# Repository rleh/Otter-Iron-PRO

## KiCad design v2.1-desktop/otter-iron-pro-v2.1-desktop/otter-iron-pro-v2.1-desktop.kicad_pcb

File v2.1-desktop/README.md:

# Otter-Iron-PRO v2.1-desktop

is variant of the _Otter-Iron-PRO v2.0_ designed for desktop-use.

Additional to/instead of USB-PD is can be supplied from any lab power supply with ?? to ?? V.
A cheap switch-mode mains power supply works as well, a stackable enclosure for a  _Meanwell RPS-???_ will be designed in the future.

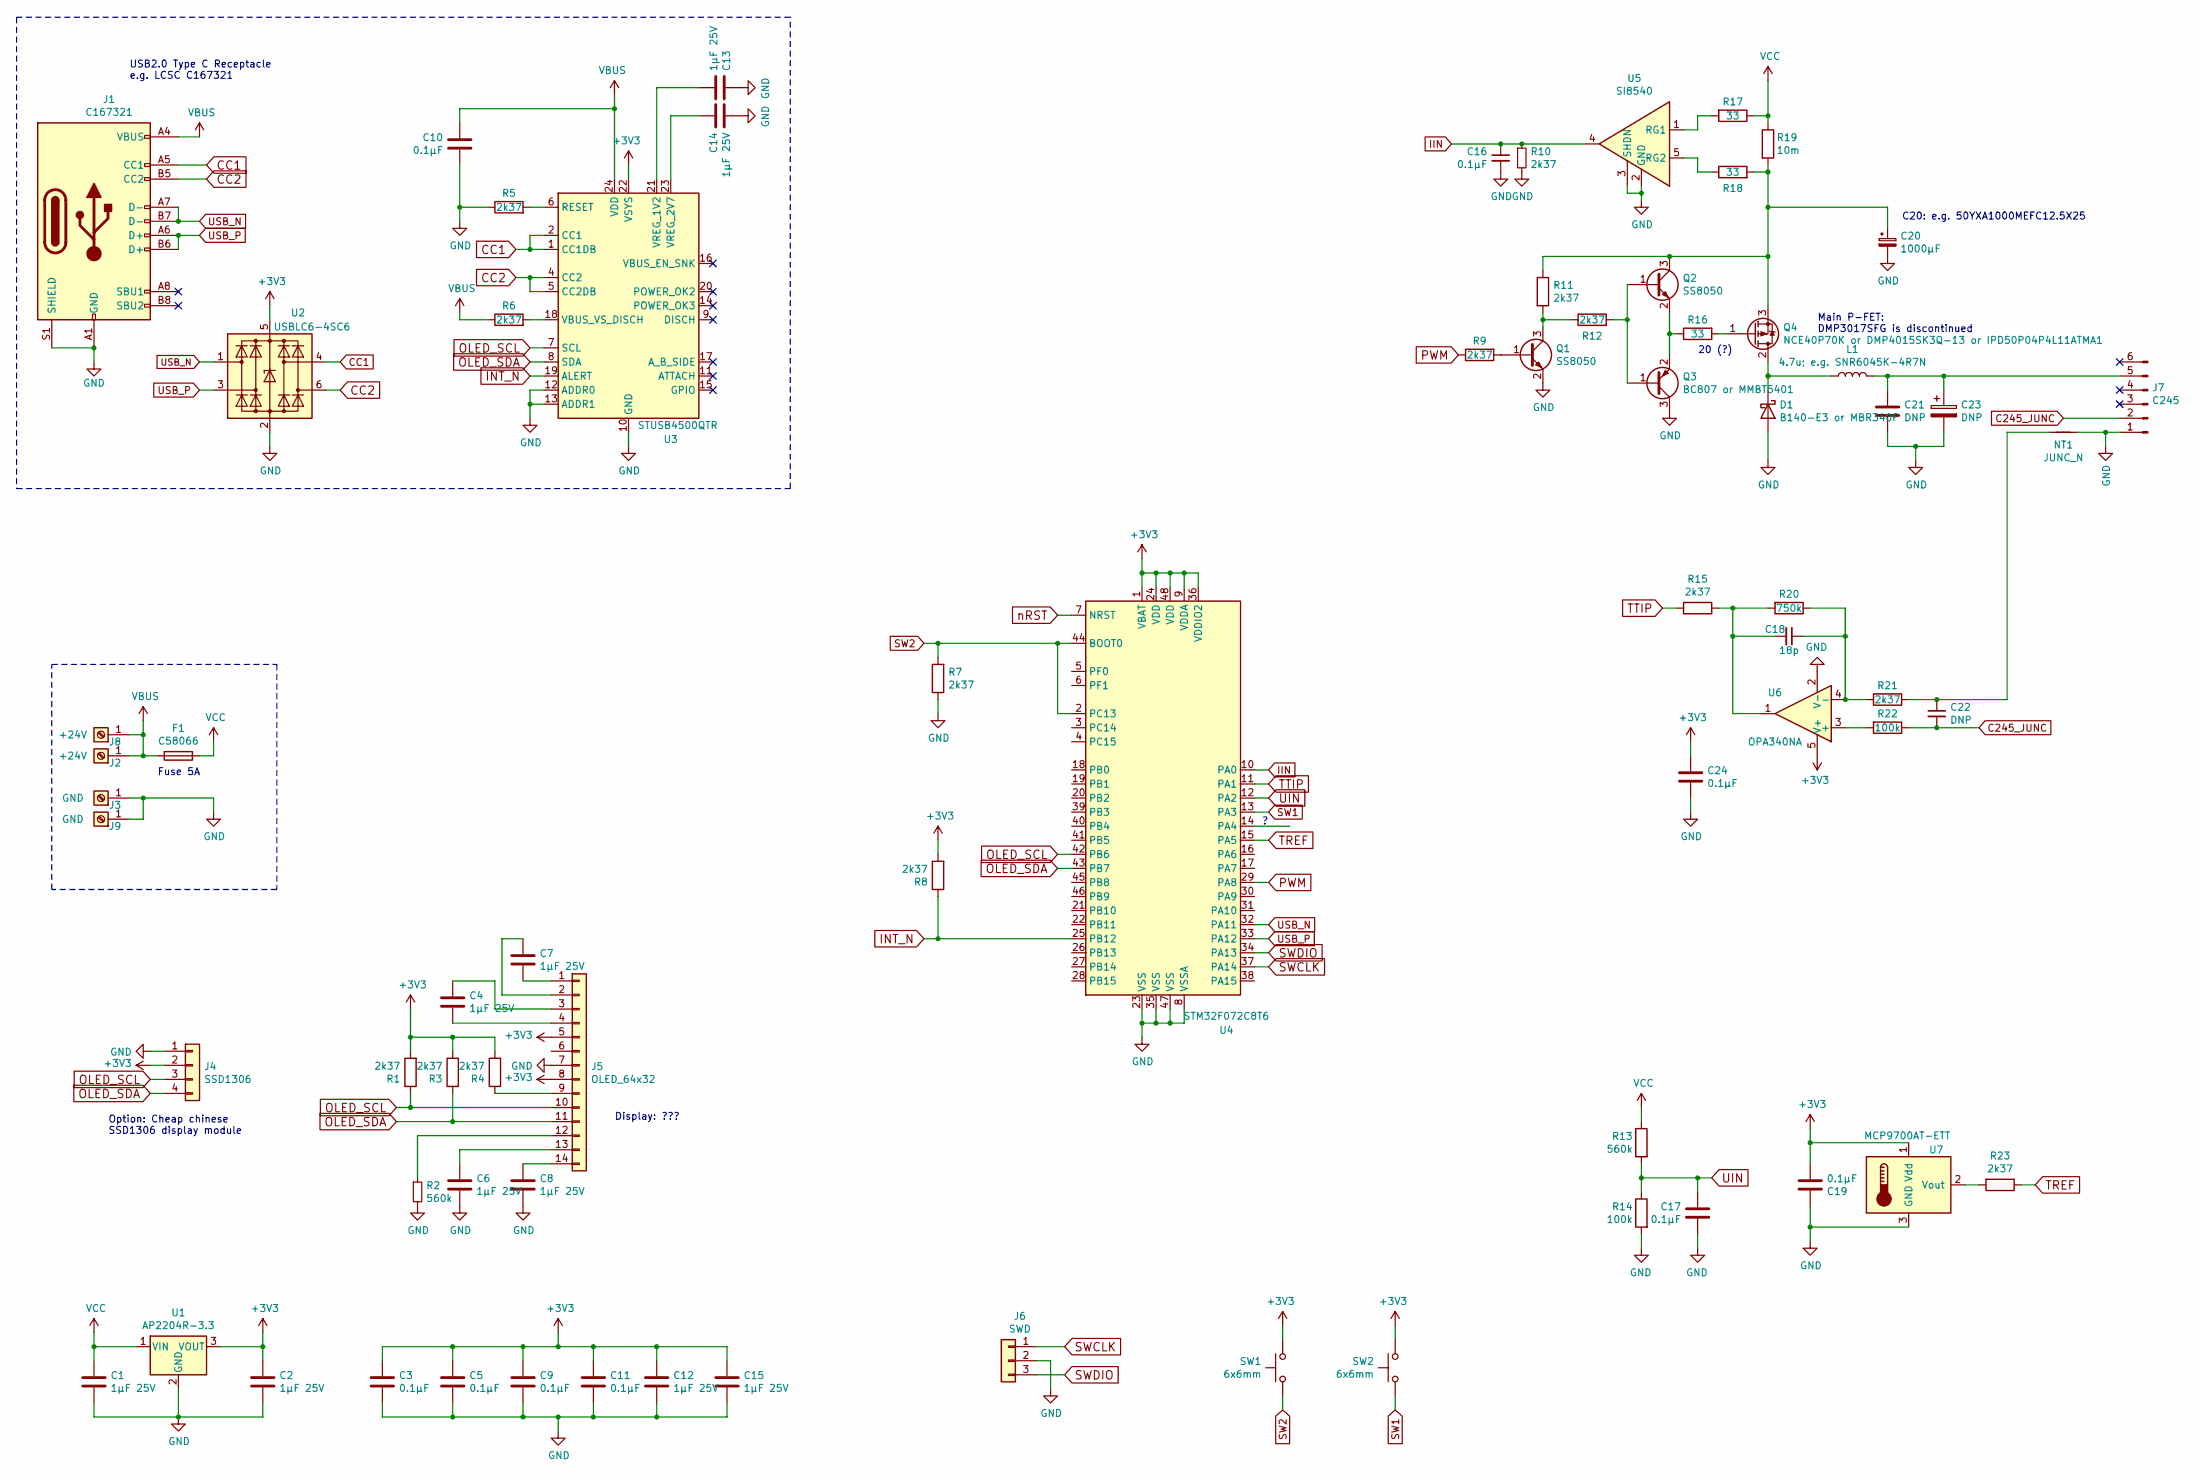
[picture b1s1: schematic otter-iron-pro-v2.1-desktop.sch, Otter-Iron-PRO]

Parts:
C1, C2, C4, C6, C7, C8, C12, C13, C14, C15: 1μF 25V; C_0603_1608Metric; LCSC C115388
C3, C5, C9, C10, C11, C16, C17, C19, C24: 0.1μF; C_0603_1608Metric; LCSC C30926
C18: 18p; C_0603_1608Metric; LCSC C126551
C20: 1000µF; CP_Radial_D12.5mm_P5.00mm; LCSC C178713
C21, C22: DNP; C_0603_1608Metric
C23: DNP; CP_Radial_D8.0mm_P3.50mm
D1: B140-E3 or MBR340F; D_SOD-123F; LCSC C475721
F1: C58066; Fuseholder_Cylinder-5x20mm_Stelvio-Kontek_PTF78_Horizontal_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; LCSC C58066
J1: C167321; USB_C_Receptacle_Palconn_UTC16-G; LCSC C167321
J2: +24V; Test_Jack_4mm
J3: GND; Test_Jack_4mm
J4: SSD1306; PinHeader_1x04_P2.54mm_Vertical
J5: OLED_64x32; OLED_SSD1306_14pin
J6: SWD; Molex_KK-254_AE-6410-03A_1x03_P2.54mm_Vertical
J7: C245; RPC1-12RB-6P(71)
J8: +24V; Banana_Jack_1Pin
J9: GND; Banana_Jack_1Pin
L1: 4.7u; e.g. SNR6045K-4R7N; L_Taiyo-Yuden_NR-60xx; LCSC C326336
NT1: JUNC_N; NetTie-2_SMD_Pad0.5mm
Q1, Q2: SS8050; SOT-23; LCSC C2150
Q3: BC807 or MMBT5401; SOT-23; LCSC C8326
Q4: NCE40P70K or DMP4015SK3Q-13 or IPD50P04P4L11ATMA1; TO-252-2; LCSC C130101
R1, R3, R4, R5, R6, R7, R8, R9, R10, R11, R12, R15, R21, R23: 2k37; R_0603_1608Metric; LCSC C25964
R2, R13: 560k; R_0603_1608Metric; LCSC C23203
R14, R22: 100k; R_0603_1608Metric; LCSC C15458
R16, R17, R18: 33; R_0603_1608Metric; LCSC C23140
R19: 10m; R_1206_3216Metric; LCSC C104920
R20: 750k; R_0603_1608Metric; LCSC C26005
SW1, SW2: 6x6mm; SW_PUSH_6mm_H13mm; LCSC C493026
U1: AP2204R-3.3; SOT-89-3; LCSC C156303
U2: USBLC6-4SC6; SOT-23-6; LCSC C111212
U3: STUSB4500QTR; QFN-24-1EP_4x4mm_P0.5mm_EP2.7x2.7mm; LCSC C506650
U4: STM32F072C8T6; LQFP-48_7x7mm_P0.5mm; LCSC C80488
U5: SI8540; SOT-23-5
U6: OPA340NA; SOT-23-5; LCSC C73479
U7: MCP9700AT-ETT; SOT-23; LCSC C127949

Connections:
+3V3: C2.1, C3.1, C5.1, C9.1, C11.1, C12.1, C15.1, C19.1, C24.1, J4.2, J5.5, J5.8, R1.2, R3.2, R4.2, R8.2, SW1.1, SW2.1, U1.3 (VOUT), U2.5 (VBUS), U3.22 (VSYS), U4.1 (VBAT), U4.9 (VDDA), U4.24 (VDD), U4.36 (VDDIO2), U4.48 (VDD), U6.5 (V+), U7.1 (Vdd)
C245_JUNC: C22.2, J7.2, R22.1
CC1: J1.A5 (CC1), U2.4 (I/O3), U3.1 (CC1DB), U3.2 (CC1)
CC2: J1.B5 (CC2), U2.6 (I/O4), U3.4 (CC2), U3.5 (CC2DB)
GND: C1.2, C2.2, C3.2, C5.2, C6.2, C8.2, C9.2, C10.2, C11.2, C12.2, C13.1, C14.2, C15.2, C16.2, C17.2, C19.2, C20.2, C21.2, C23.2, C24.2, D1.2 (A), J1.A1 (GND), J1.A12 (GND), J1.B1 (GND), J1.B12 (GND), J1.S1 (SHIELD), J3.1, J4.1, J5.7, J6.2, J7.1, J9.1, NT1.2, Q1.2 (E), Q3.3 (C), R2.2, R5.1, R7.1, R10.2, R14.2, U1.2 (GND), U2.2 (GND), U3.10 (GND), U3.12 (ADDR0), U3.13 (ADDR1), U3.25 (GND), U4.8 (VSSA), U4.23 (VSS), U4.35 (VSS), U4.47 (VSS), U5.2 (GND), U5.3 (SHDN), U6.2 (V-), U7.3 (GND)
IIN: C16.1, R10.1, U4.10 (PA0), U5.4
INT_N: R8.1, U3.19 (ALERT), U4.25 (PB12)
unnamed: C4.1, J5.3
unnamed: C4.2, J5.4
unnamed: C6.1, J5.13
unnamed: C7.1, J5.2
unnamed: C7.2, J5.1
unnamed: C8.1, J5.14
unnamed: C13.2, U3.21 (VREG_1V2)
unnamed: C14.1, U3.23 (VREG_2V7)
unnamed: C18.1, R20.1, R21.2, U6.4 (-)
unnamed: C18.2, R15.1, R20.2, U6.1
unnamed: C20.1, Q2.3 (C), Q4.3 (S), R11.1, R18.2, R19.2
unnamed: C21.1, C23.1, J7.5, L1.2
unnamed: C22.1, NT1.1, R21.1
unnamed: D1.1 (K), L1.1, Q4.2 (D)
unnamed: J5.9, R4.1
unnamed: J5.12, R2.1
unnamed: Q1.1 (B), R9.2
unnamed: Q1.3 (C), R11.2, R12.1
unnamed: Q2.1 (B), Q3.1 (B), R12.2
unnamed: Q2.2 (E), Q3.2 (E), R16.1
unnamed: Q4.1 (G), R16.2
unnamed: R5.2, U3.6 (RESET)
unnamed: R6.2, U3.18 (VBUS_VS_DISCH)
unnamed: R17.2, U5.1 (RG1)
unnamed: R18.1, U5.5 (RG2)
unnamed: R22.2, U6.3 (+)
unnamed: R23.2, U7.2 (Vout)
OLED_SCL: J4.3, J5.10, R1.1, U3.7 (SCL), U4.42 (PB6)
OLED_SDA: J4.4, J5.11, R3.1, U3.8 (SDA), U4.43 (PB7)
PWM: R9.1, U4.29 (PA8)
SW1: SW2.2, U4.13 (PA3)
SW2: R7.2, SW1.2, U4.2 (PC13), U4.44 (BOOT0)
SWCLK: J6.1, U4.37 (PA14)
SWDIO: J6.3, U4.34 (PA13)
TREF: R23.1, U4.15 (PA5)
TTIP: R15.2, U4.11 (PA1)
UIN: C17.1, R13.2, R14.1, U4.12 (PA2)
USB_N: J1.A7 (D-), J1.B7 (D-), U2.1 (I/O1), U4.32 (PA11)
USB_P: J1.A6 (D+), J1.B6 (D+), U2.3 (I/O2), U4.33 (PA12)
VBUS: C10.1, F1.2, J1.A4 (VBUS), J1.A9 (VBUS), J1.B4 (VBUS), J1.B9 (VBUS), J2.1, J8.1, R6.1, U3.24 (VDD)
VCC: C1.1, F1.1, R13.1, R17.1, R19.1, U1.1 (VIN)

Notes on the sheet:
20 (?)
Option: Cheap chinese SSD1306 display module
Display: ???
Fuse 5A
USB2.0 Type C Receptacle e.g. LCSC C167321
Main P-FET: DMP3017SFG is discontinued
C20: e.g. 50YXA1000MEFC12.5X25

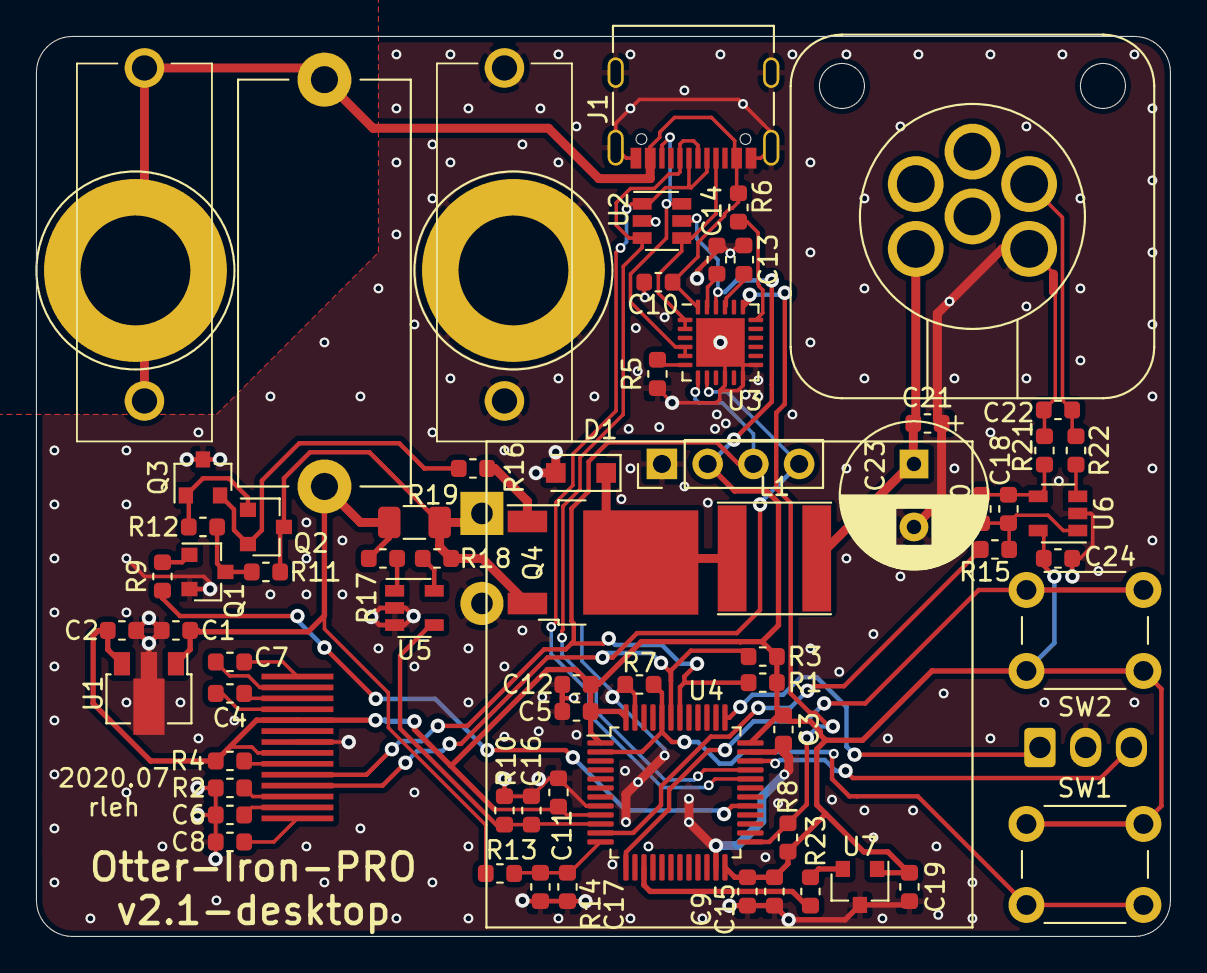
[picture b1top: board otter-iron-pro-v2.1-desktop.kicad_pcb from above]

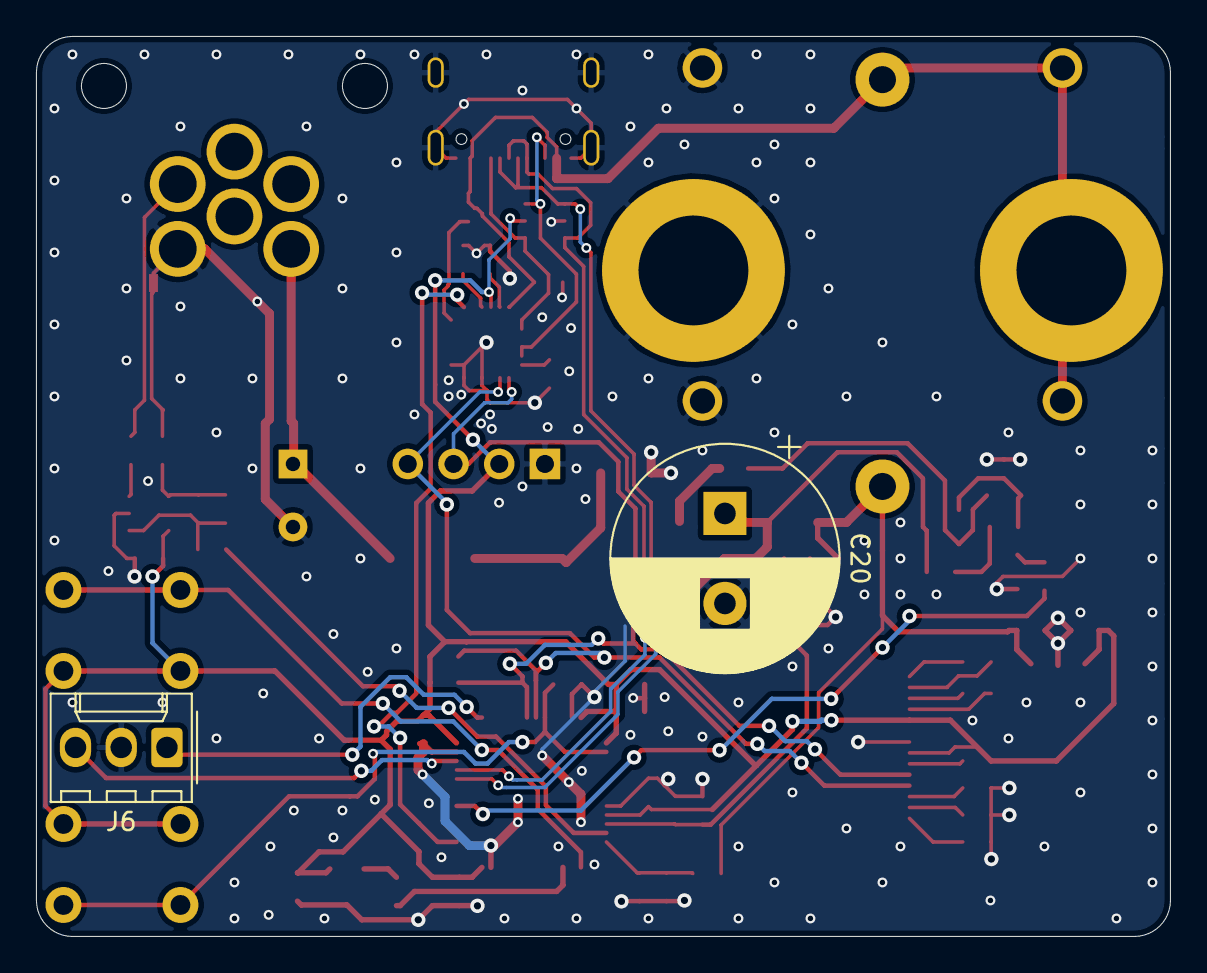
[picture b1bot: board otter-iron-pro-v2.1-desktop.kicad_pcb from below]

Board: 2 copper layers, 63.0 x 50.0 mm, 73 parts (2 on the bottom side), 48 nets.

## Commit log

2020-07-03 Create variant v2.1-desktop
2020-07-03 Import v2.0 schematics
2020-07-03 Consolidate schematics into a single sheet
2020-07-04 Finish schematic, start layouting...
2020-07-06 Layout draft
2020-07-12 Finish layout
2020-07-12 Silkscreen and GND area fill
2020-07-12 Export gerbers; Add LCSC part numbers
2020-12-21 initial commit on new modm based firmware: - display works, but update rate is slow at 400kHz, should try increasing in future - buttons adjust temp setpoint, but are mirrord - ADC samples incorrect 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
2020-12-22 AdcSampler WIP...
2020-12-23 ... tuned.
2020-12-23 firmware_modm: Add gitignore
2021-01-10 Changed controller to outputting power [W] instead of duty cycle, limiting total output power, disabling output pwm before sampling ADC
2021-03-04 bug fixed in i2c
2021-03-09 functional USB-PD (kind of... we dont understand how, but it works - and we didnt touch a single page of USB standard)...
    some kind of menue for selecting input current limit if no USB-PD
    general bug fixes and useability improvements
2021-03-09 Use upstreamed modm::Stusb4500 driver
